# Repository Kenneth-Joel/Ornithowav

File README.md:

# Ornithowav
 A 'Bird Sensor'

## This Repository Contains
	1. brd20 : a modified version of kws20.py found in ai8x-training library
	2. brd20_demo : Based on the KWS20 example, A MAX78000 C Project that can be flashed to a board. No need for any external hardware to run this demo
	3. Synthesized-C-Code : Output of the synthesis script
	4. DataEngineering-Python : Python DSP Scripts used for Data Engineering, mainly resampling and slicing.
	5. Hardware Design Files : Contains PCB Design Files (schemaitc, board, step and renders) 
	6. Test Samples Used in Video Demo

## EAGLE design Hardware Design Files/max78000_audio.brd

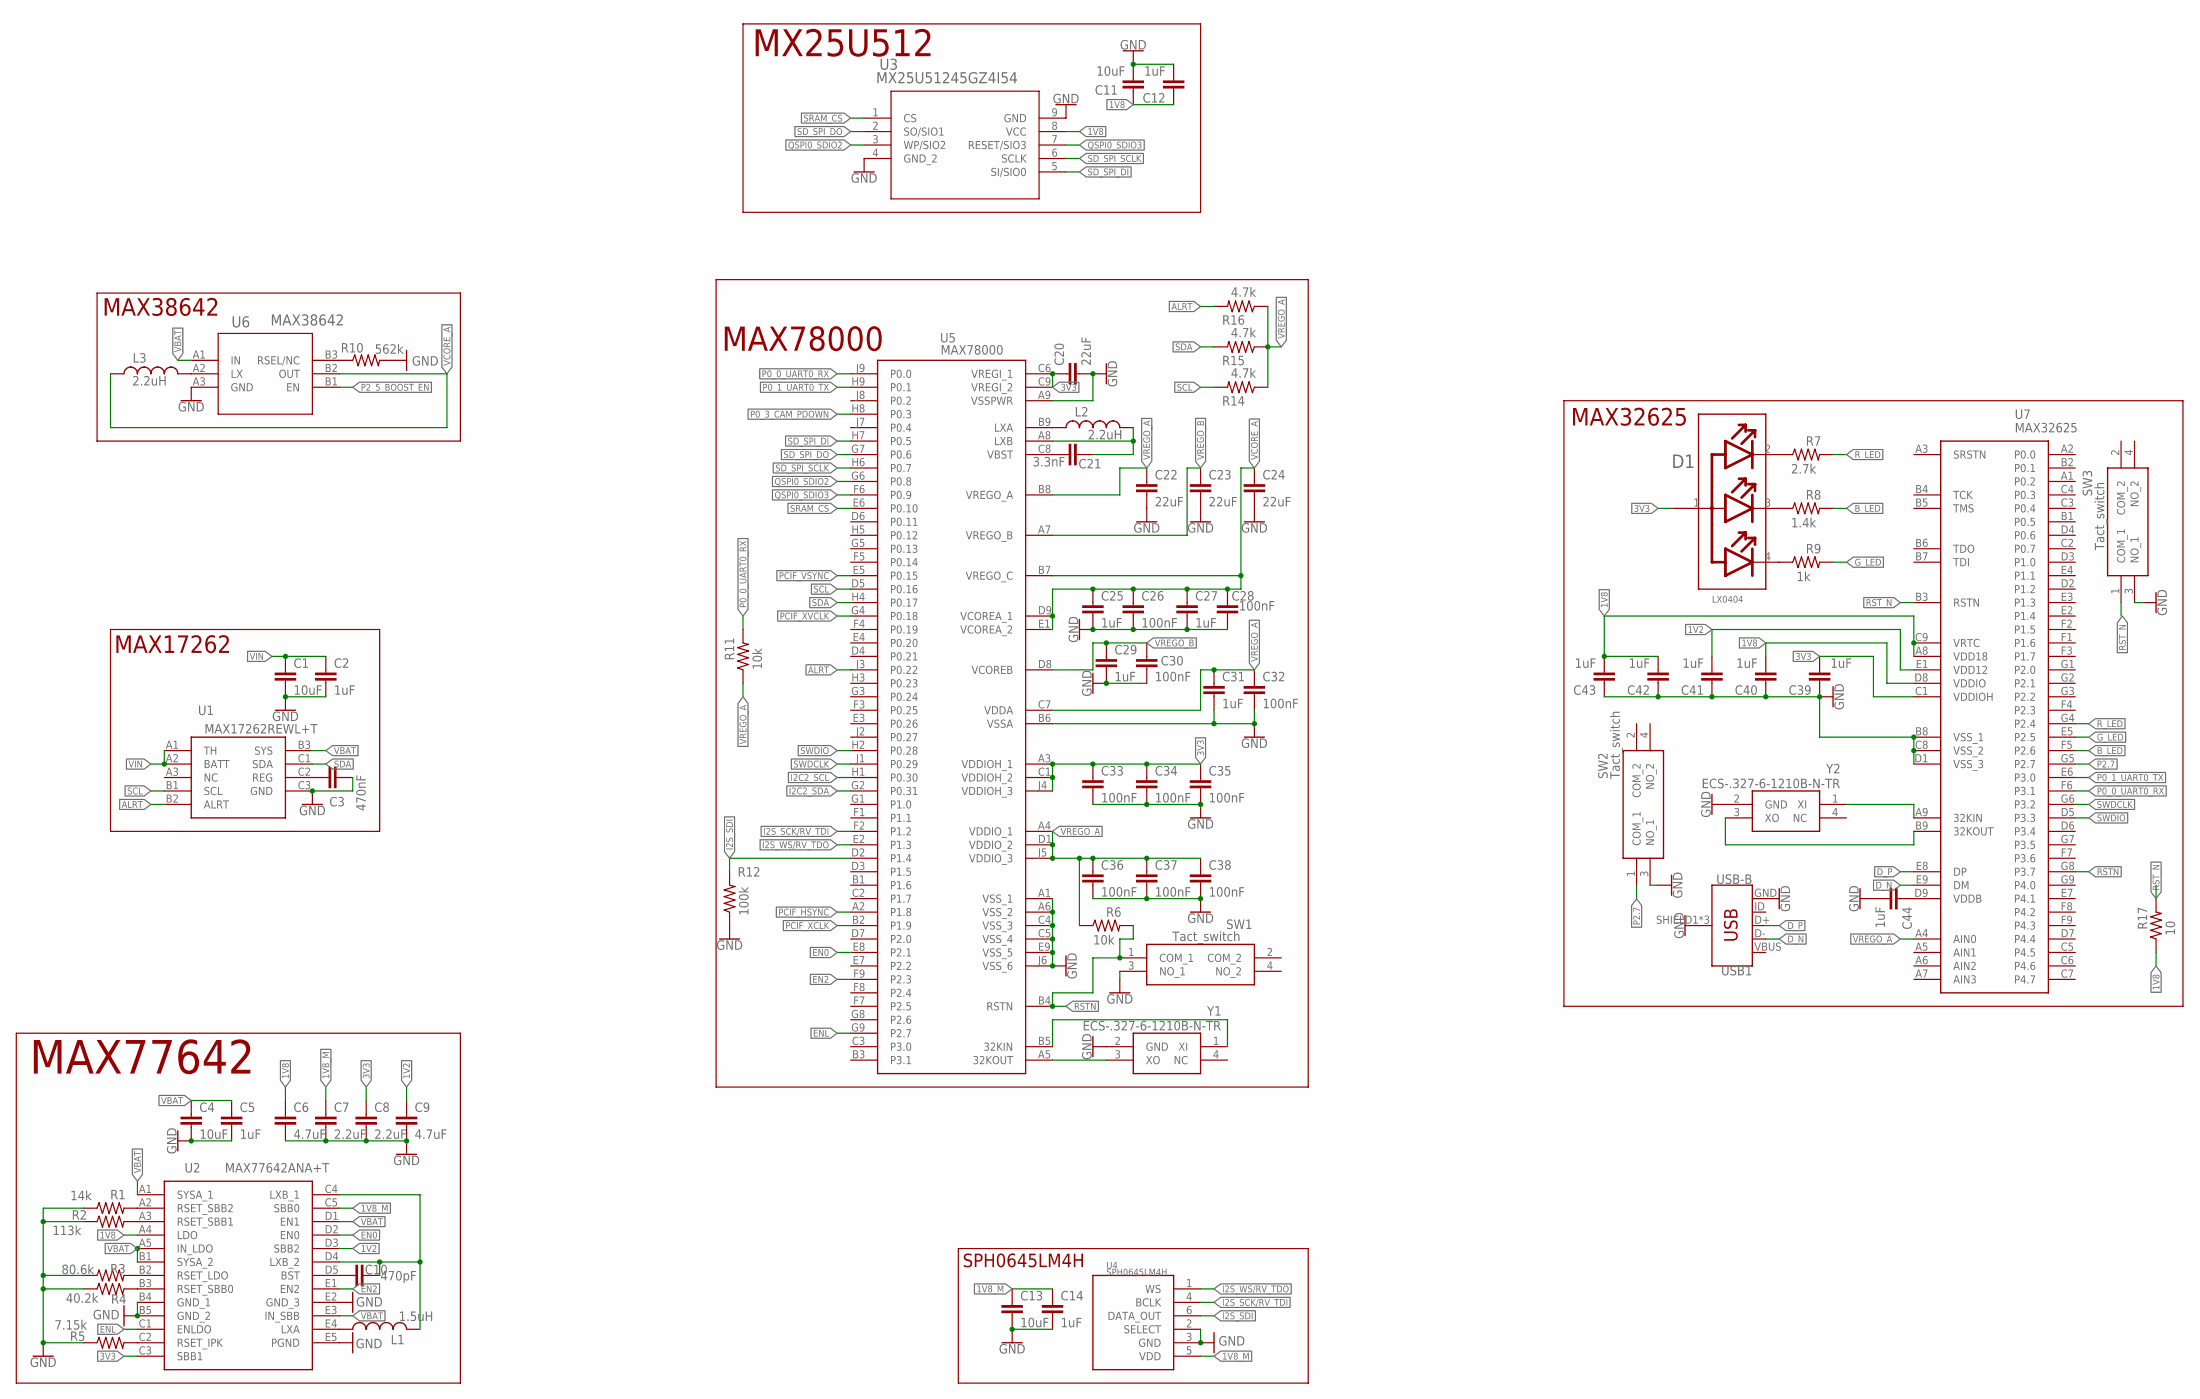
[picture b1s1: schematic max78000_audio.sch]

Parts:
C1, C4, C13: 10uF; 0402
C2, C5, C14, C39, C40, C41, C42, C43, C44: 1uF; 0201
C3: 470nF; 0201
C6, C9: 4.7uF; 0402
C7, C8: 2.2uF; 0402
C10: 470pF; 0402
C11: 10uF; 0201
C12, C25, C27, C29, C31: 1uF; 0402
C20, C22, C23, C24: 22uF; 0603
C21: 3.3nF; 0201
C26, C28, C30, C32, C33, C34, C35, C36, C37, C38: 100nF; 0201
D1: LX0404; LUMEX_SML-LX0404SIUPGUSB_0
L1: 1.5uH; 0504
L2, L3: 2.2uH; 0805
R1: 14k; 0201
R2: 113k; 0201
R3: 80.6k; 0201
R4: 40.2k; 0201
R5: 7.15k; 0201
R6, R11: 10k; 0201
R7: 2.7k; 0201
R8: 1.4k; 0201
R9: 1k; 0201
R10: 562k; 0201
R12: 100k; 0201
R14, R15, R16: 4.7k; 0201
R17: 10; 0201
SW1, SW2, SW3: Tact_switch; PTS815SJM250SMTRLFS
U1: MAX17262REWL+T; BGA9C40P3X3_147X145X69
U2: MAX77642ANA+T; BGA25C40P5X5_206X206X50
U3: MX25U51245GZ4I54; WSON8_8X6XOP8_MAC
U4: SPH0645LM4H; KNOWLES_SPH0645LM4H-B_0
U5: MAX78000; BGA81C80P9X9_800X800X130
U6: MAX38642; 21-100128A_N60E1+2_MXM
U7: MAX32625; BGA63C40P9X7_387X307X69
USB1: USB-B; USB-B-MICRO-SMD
Y1, Y2: ECS-.327-6-1210B-N-TR; ECS32761210BNTR

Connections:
1V2: C9.1, C41.2, U2.D3 (SBB2), U7.E1 (VDD12)
1V8: C6.1, C11.1, C12.1, C40.2, C42.2, C43.2, R17.1, U2.A4 (LDO), U3.8 (VCC), U7.A8 (VDD18), U7.C9 (VRTC), U7.D8 (VDDIO)
1V8_M: C7.1, C13.1, C14.1, U2.C5 (SBB0), U4.5 (VDD)
3V3: C8.1, C20.1, C33.1, C34.1, C35.1, C39.2, D1.1 (COMMON_ANODE), U2.C3 (SBB1), U5.A3 (VDDIOH_1), U5.C1 (VDDIOH_2), U5.C6 (VREGI_1), U5.C9 (VREGI_2), U5.J4 (VDDIOH_3), U7.C1 (VDDIOH)
ALRT: R16.2, U1.B2 (ALRT), U5.J3 (P0.22)
B_LED: R8.2, U7.F5 (P2.6)
D_N: U7.E9 (DM), USB1.D-
D_P: U7.E8 (DP), USB1.D+
EN0: U2.D2 (EN0), U5.E8 (P2.1)
EN2: U2.E1 (EN2), U5.F9 (P2.3)
ENL: U2.C1 (ENLDO), U5.G9 (P2.7)
GND: C1.2, C2.2, C3.2, C4.2, C5.2, C6.2, C7.2, C8.2, C9.2, C11.2, C12.2, C13.2, C14.2, C20.2, C22.2, C23.2, C24.2, C25.2, C26.2, C27.2, C28.2, C29.2, C30.2, C31.2, C32.2, C33.2, C34.2, C35.2, C36.2, C37.2, C38.2, C39.1, C40.1, C41.1, C42.1, C43.1, C44.2, R1.1, R2.1, R3.1, R4.1, R5.1, R10.2, R12.1, SW1.3 (NO_1), SW2.3 (NO_1), SW3.3 (NO_1), U1.C3 (GND), U2.B4 (GND_1), U2.B5 (GND_2), U2.E2 (GND_3), U2.E5 (PGND), U3.4 (GND_2), U3.9 (GND), U4.2 (SELECT), U4.3 (GND), U5.A1 (VSS_1), U5.A6 (VSS_2), U5.A9 (VSSPWR), U5.B6 (VSSA), U5.C4 (VSS_3), U5.C5 (VSS_4), U5.E9 (VSS_5), U5.J6 (VSS_6), U6.A3 (GND), U7.B8 (VSS_1), U7.C8 (VSS_2), U7.D1 (VSS_3), USB1.GND, USB1.SHIELD1 (SHIELD), USB1.SHIELD2 (SHIELD), USB1.SHIELD3 (SHIELD), Y1.2 (GND), Y2.2 (GND)
G_LED: R9.2, U7.E5 (P2.5)
I2C2_SCL: U5.H1 (P0.30)
I2C2_SDA: U5.G2 (P0.31)
I2S_SCK/RV_TDI: U4.4 (BCLK), U5.F2 (P1.2)
I2S_SDI: R12.2, U4.6 (DATA_OUT), U5.D2 (P1.4)
I2S_WS/RV_TDO: U4.1 (WS), U5.E2 (P1.3)
unnamed: C21.2, L2.2, U5.A8 (LXB)
unnamed: R3.2, U2.B2 (RSET_LDO)
unnamed: R4.2, U2.B3 (RSET_SBB0)
unnamed: R5.2, U2.C2 (RSET_IPK)
unnamed: R1.2, U2.A2 (RSET_SBB2)
unnamed: R2.2, U2.A3 (RSET_SBB1)
unnamed: C10.1, U2.D5 (BST)
unnamed: L1.1, U2.E4 (LXA)
unnamed: C21.1, U5.C8 (VBST)
unnamed: U5.A5 (32KOUT), Y1.3 (XO)
unnamed: U5.B5 (32KIN), Y1.1 (XI)
unnamed: C3.1, U1.C2 (REG)
unnamed: L2.1, U5.B9 (LXA)
unnamed: U7.A9 (32KIN), Y2.1 (XI)
unnamed: U7.B9 (32KOUT), Y2.3 (XO)
unnamed: C44.1, U7.D9 (VDDB)
unnamed: D1.2 (RED_CATHODE), R7.1
unnamed: D1.3 (BLUE_CATHODE), R8.1
unnamed: D1.4 (GREEN_CATHODE), R9.1
unnamed: L3.2, U6.A2 (LX)
unnamed: R10.1, U6.B3 (RSEL/NC)
unnamed: C10.2, L1.2, U2.C4 (LXB_1), U2.D4 (LXB_2)
P0_0_UART0_RX: R11.2, U5.J9 (P0.0), U7.F6 (P3.1)
P0_1_UART0_TX: U5.H9 (P0.1), U7.E6 (P3.0)
P0_3_CAM_PDOWN: U5.H8 (P0.3)
P2.7: SW2.1 (COM_1), U7.G5 (P2.7)
P2_5_BOOST_EN: U6.B1 (EN)
PCIF_HSYNC: U5.A2 (P1.8)
PCIF_VSYNC: U5.E5 (P0.15)
PCIF_XCLK: U5.B2 (P1.9)
PCIF_XVCLK: U5.G4 (P0.18)
QSPI0_SDIO2: U3.3 (WP/SIO2), U5.G6 (P0.8)
QSPI0_SDIO3: U3.7 (RESET/SIO3), U5.F6 (P0.9)
RSTN: R6.2, SW1.1 (COM_1), U5.B4 (RSTN), U7.G8 (P3.7)
RST_N: R17.2, SW3.1 (COM_1), U7.B3 (RSTN)
R_LED: R7.2, U7.G4 (P2.4)
SCL: R14.2, U1.B1 (SCL), U5.D5 (P0.16)
SDA: R15.2, U1.C1 (SDA), U5.H4 (P0.17)
SD_SPI_DI: U3.5 (SI/SIO0), U5.H7 (P0.5)
SD_SPI_DO: U3.2 (SO/SIO1), U5.G7 (P0.6)
SD_SPI_SCLK: U3.6 (SCLK), U5.H6 (P0.7)
SRAM_CS: U3.1 (CS), U5.E6 (P0.10)
SWDCLK: U5.J1 (P0.29), U7.G6 (P3.2)
SWDIO: U5.H2 (P0.28), U7.D5 (P3.3)
VBAT: C4.1, C5.1, U1.B3 (SYS), U2.A1 (SYSA_1), U2.A5 (IN_LDO), U2.B1 (SYSA_2), U2.D1 (EN1), U2.E3 (IN_SBB), U6.A1 (IN)
VBUS: USB1.VBUS
VCORE_A: C24.1, C25.1, C26.1, C27.1, C28.1, L3.1, U5.B7 (VREGO_C), U5.D9 (VCOREA_1), U5.E1 (VCOREA_2), U6.B2 (OUT)
VIN: C1.1, C2.1, U1.A1 (TH), U1.A2 (BATT)
VREGO_A: C22.1, C31.1, C32.1, C36.1, C37.1, C38.1, R6.1, R11.1, R14.1, R15.1, R16.1, U5.A4 (VDDIO_1), U5.B8 (VREGO_A), U5.C7 (VDDA), U5.D1 (VDDIO_2), U5.J5 (VDDIO_3), U7.A4 (AIN0)
VREGO_B: C23.1, C29.1, C30.1, U5.A7 (VREGO_B), U5.D8 (VCOREB)

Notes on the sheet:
MAX77642
MAX17262
MX25U512
MAX78000
MAX32625
MAX38642
SPH0645LM4H

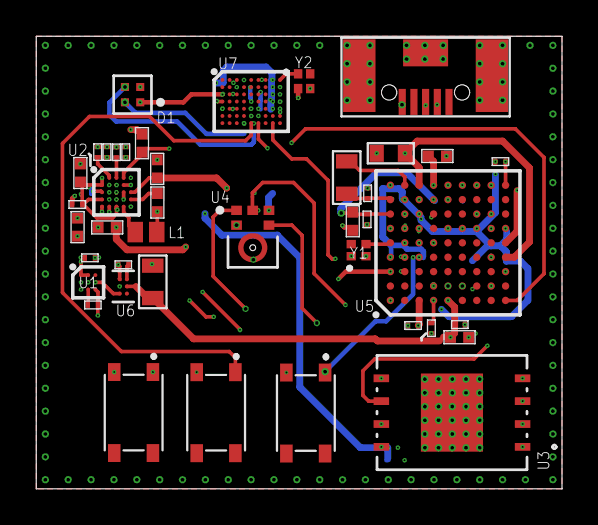
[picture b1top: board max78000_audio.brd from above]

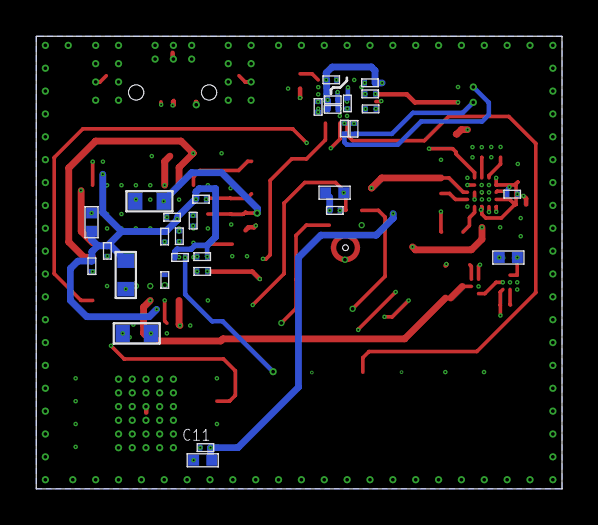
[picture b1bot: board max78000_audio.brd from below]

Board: 6 copper layers, 29.2 x 25.1 mm, 72 parts (31 on the bottom side), 59 nets.

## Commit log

2022-10-27 Updated README file
2022-10-27 Added Project Report

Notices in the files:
parts and their libraries:
COPYRIGHT: Copyright (C) 2018 Accelerated Designs. All rights reserved
Sensio-PowerSymbols: Licensing: Creative Commons ShareAlike 4.0 International - https://creativecommons.org/licenses/by-sa/4.0
